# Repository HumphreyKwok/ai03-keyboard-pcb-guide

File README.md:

# A Type-C Version of ai03's Keyboard PCB Guide

Based on ai03's keyboard PCB guide and other few open sourced keyboard pcbs. </br>
I made an upgrade version with a usb type-c connector.

### Directory Lists
* ai03-pad-original </br>
The original contents of the guide created by ai03, including the schematic symbols and footprints libraries.

* ai03-pad-duplicate </br>
Simply a duplicated version of the oringinal PCB, I tried to recreate it step by step.

* ai03-pad-type-c </br>
The upgraded (?) version of the pad, with type-c connector.

### Useful Resources

* ai03's original guide: </br>
https://wiki.ai03.me/books/pcb-design/chapter/pcb-designer-guide

* KiCAD guide provided by Digi-Key: </br>
https://youtu.be/vaCVh2SAZY4

### Type-C QMK Keyboards I Used for References
* Plain60-c: </br>
https://github.com/Maartenwut/plain60-c

* Mullet: </br>
https://github.com/coseyfannitutti/mullet

* Remeo: </br>
https://github.com/coseyfannitutti/romeo

* CO60: </br>
https://github.com/jmdaly/CO60

This is where all my journeys starts, thanks to the community. </br>
Good luck :)

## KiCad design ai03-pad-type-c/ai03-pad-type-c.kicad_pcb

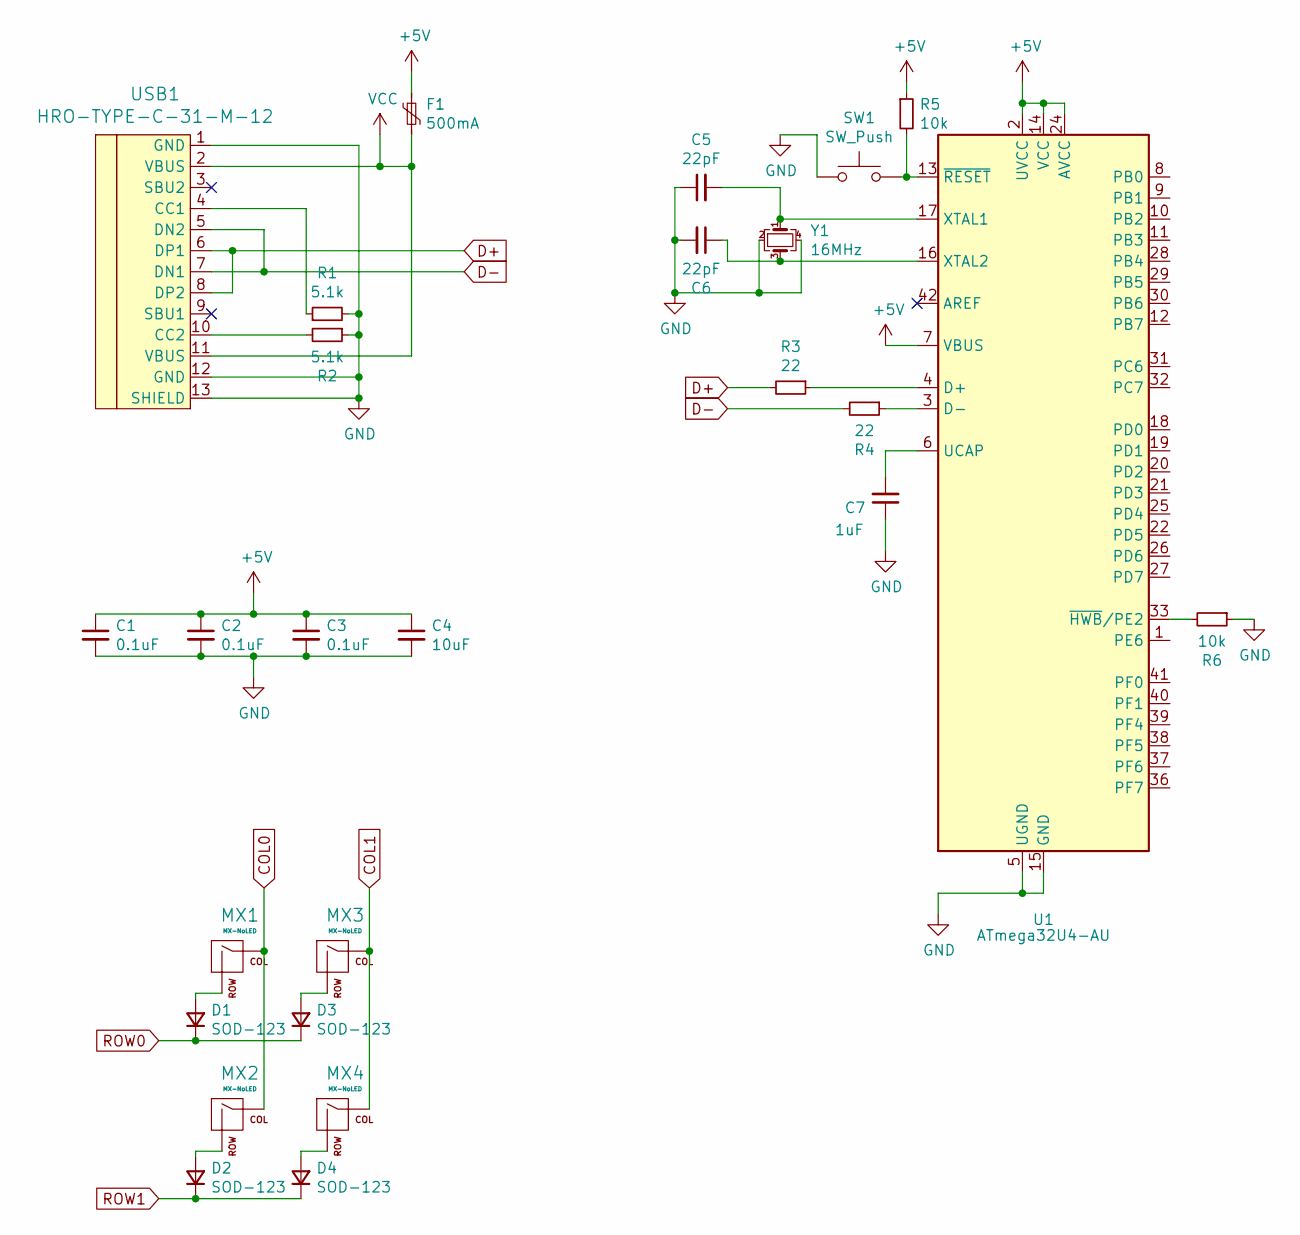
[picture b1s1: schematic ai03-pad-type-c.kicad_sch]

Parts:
C1, C2, C3: 0.1uF; C_0805_2012Metric
C4: 10uF; C_0805_2012Metric
C5, C6: 22pF; C_0805_2012Metric
C7: 1uF; C_0805_2012Metric
D1, D2, D3, D4: SOD-123; D_SOD-123
F1: 500mA; Fuse_1206_3216Metric
MX1, MX2, MX3, MX4: MX-NoLED; MXOnly-1U-NoLED
R1, R2: 5.1k; R_0805_2012Metric
R3, R4: 22; R_0805_2012Metric
R5, R6: 10k; R_0805_2012Metric
SW1: SW_Push; SKQG-1155865
U1: ATmega32U4-AU; TQFP-44_10x10mm_P0.8mm
USB1: HRO-TYPE-C-31-M-12
Y1: 16MHz; Crystal_SMD_3225-4Pin_3.2x2.5mm

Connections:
+5V: C1.1, C2.1, C3.1, C4.1, F1.1, R5.1, U1.2 (UVCC), U1.7 (VBUS), U1.14 (VCC), U1.24 (AVCC), U1.34 (VCC), U1.44 (AVCC)
COL0: MX1.1 (COL), MX2.1 (COL), U1.10 (PB2)
COL1: MX3.1 (COL), MX4.1 (COL), U1.8 (PB0)
D+: R3.2, USB1.6 (DP1), USB1.8 (DP2)
D-: R4.2, USB1.5 (DN2), USB1.7 (DN1)
GND: C1.2, C2.2, C3.2, C4.2, C5.1, C6.2, C7.1, R1.2, R2.1, R6.1, SW1.1, U1.5 (UGND), U1.15 (GND), U1.23 (GND), U1.35 (GND), U1.43 (GND), USB1.1 (GND), USB1.12 (GND), USB1.13 (SHIELD), Y1.2, Y1.4
unnamed: C5.2, U1.17 (XTAL1), Y1.1
unnamed: C6.1, U1.16 (XTAL2), Y1.3
unnamed: C7.2, U1.6 (UCAP)
unnamed: D1.2 (A), MX1.2 (ROW)
unnamed: D2.2 (A), MX2.2 (ROW)
unnamed: D3.2 (A), MX3.2 (ROW)
unnamed: D4.2 (A), MX4.2 (ROW)
unnamed: R1.1, USB1.4 (CC1)
unnamed: R2.2, USB1.10 (CC2)
unnamed: R3.1, U1.4 (D+)
unnamed: R4.1, U1.3 (D-)
unnamed: R5.2, SW1.2, U1.13 (~RESET)
unnamed: R6.2, U1.33 (~HWB~/PE2)
ROW0: D1.1 (K), D3.1 (K), U1.9 (PB1)
ROW1: D2.1 (K), D4.1 (K), U1.11 (PB3)
VCC: F1.2, USB1.2 (VBUS), USB1.11 (VBUS)

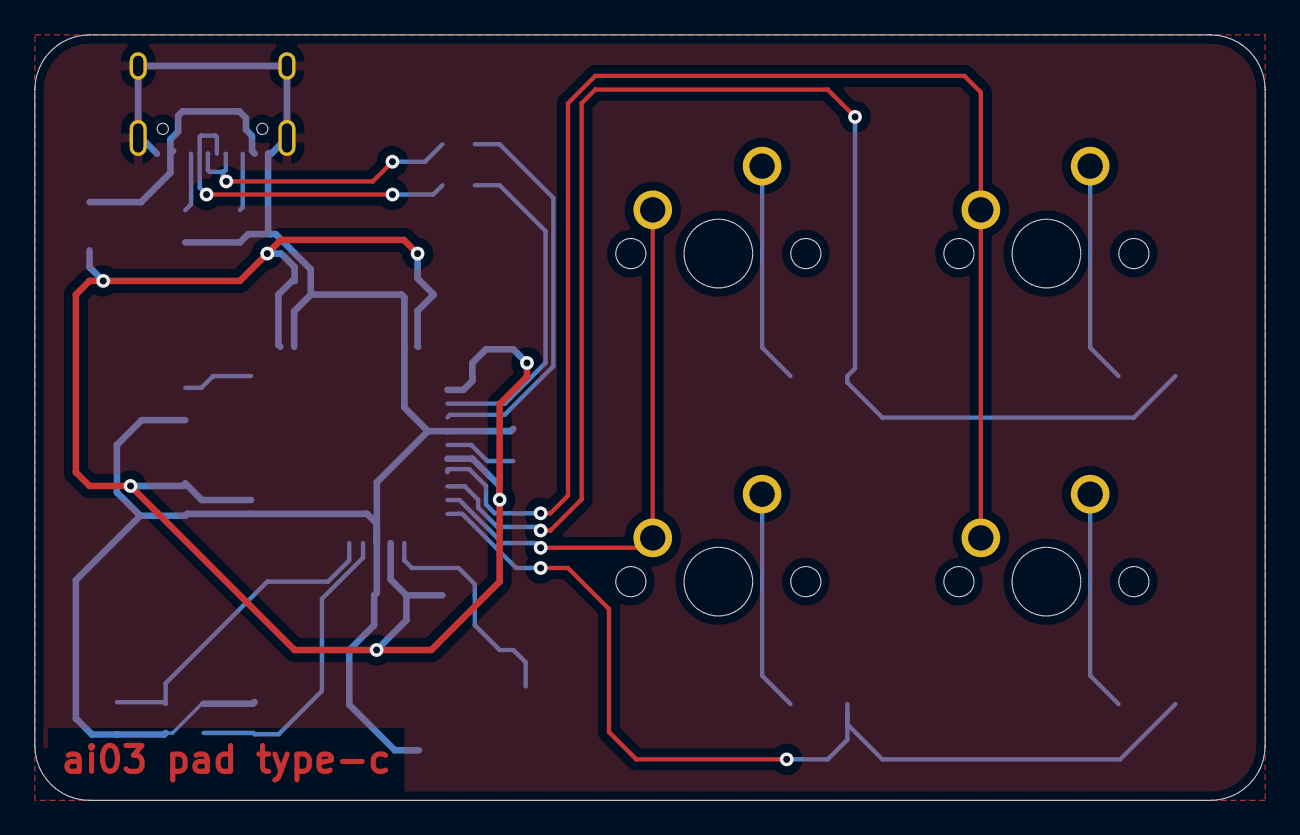
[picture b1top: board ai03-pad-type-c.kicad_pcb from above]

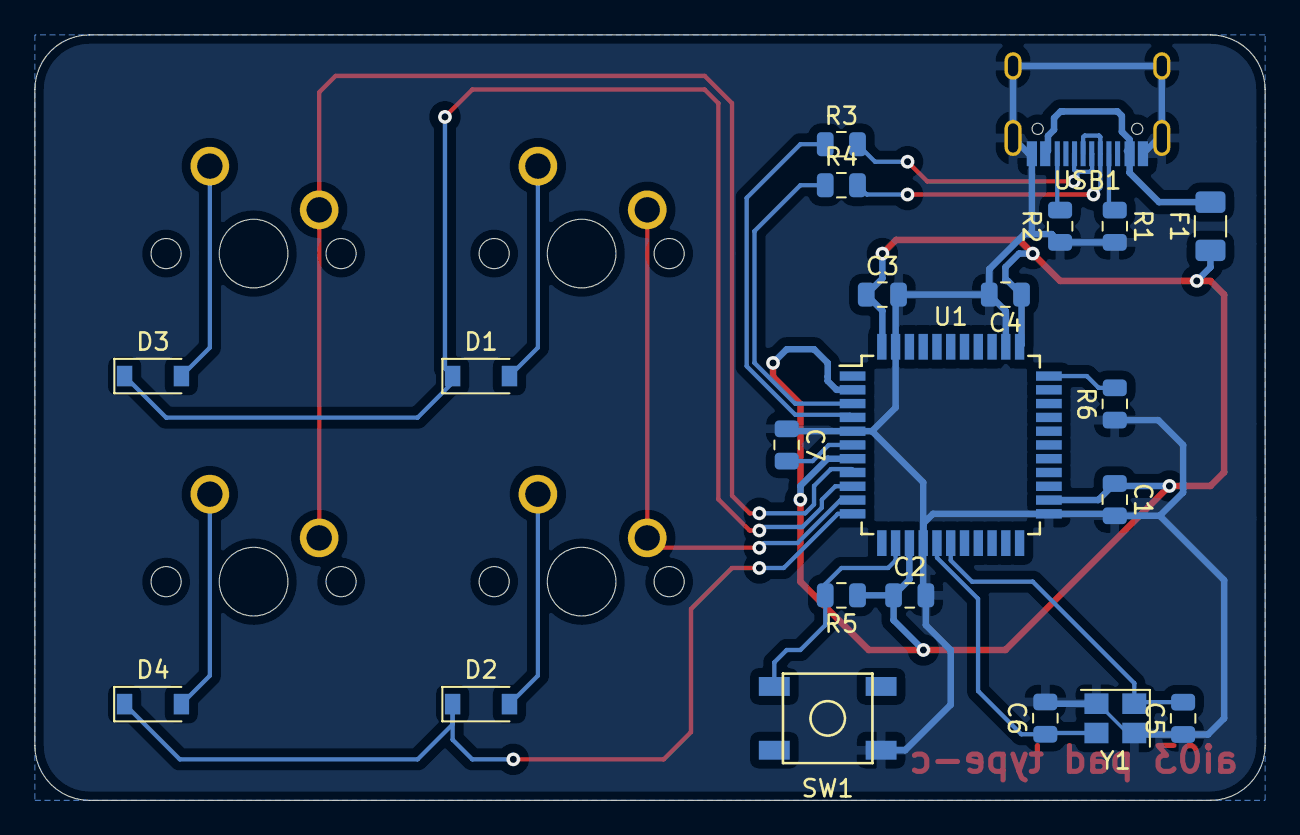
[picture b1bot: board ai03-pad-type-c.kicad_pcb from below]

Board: 2 copper layers, 71.4 x 44.5 mm, 26 parts (22 on the bottom side), 22 nets.

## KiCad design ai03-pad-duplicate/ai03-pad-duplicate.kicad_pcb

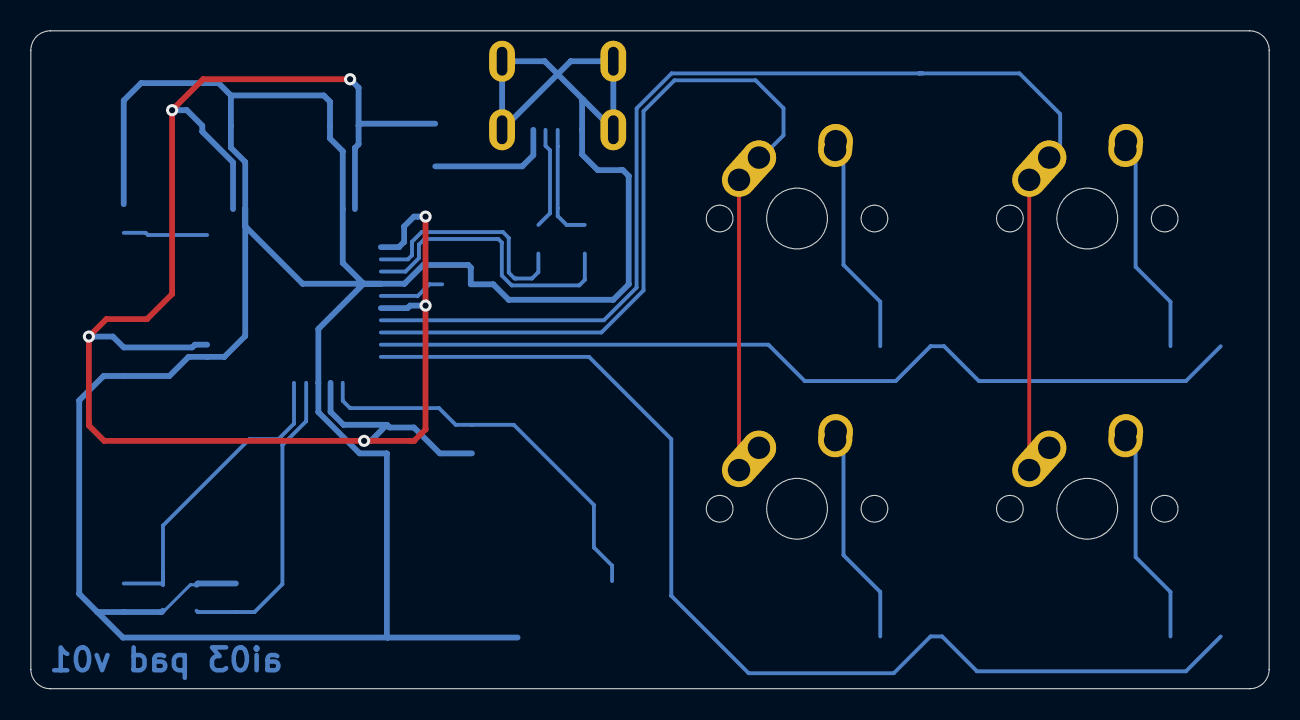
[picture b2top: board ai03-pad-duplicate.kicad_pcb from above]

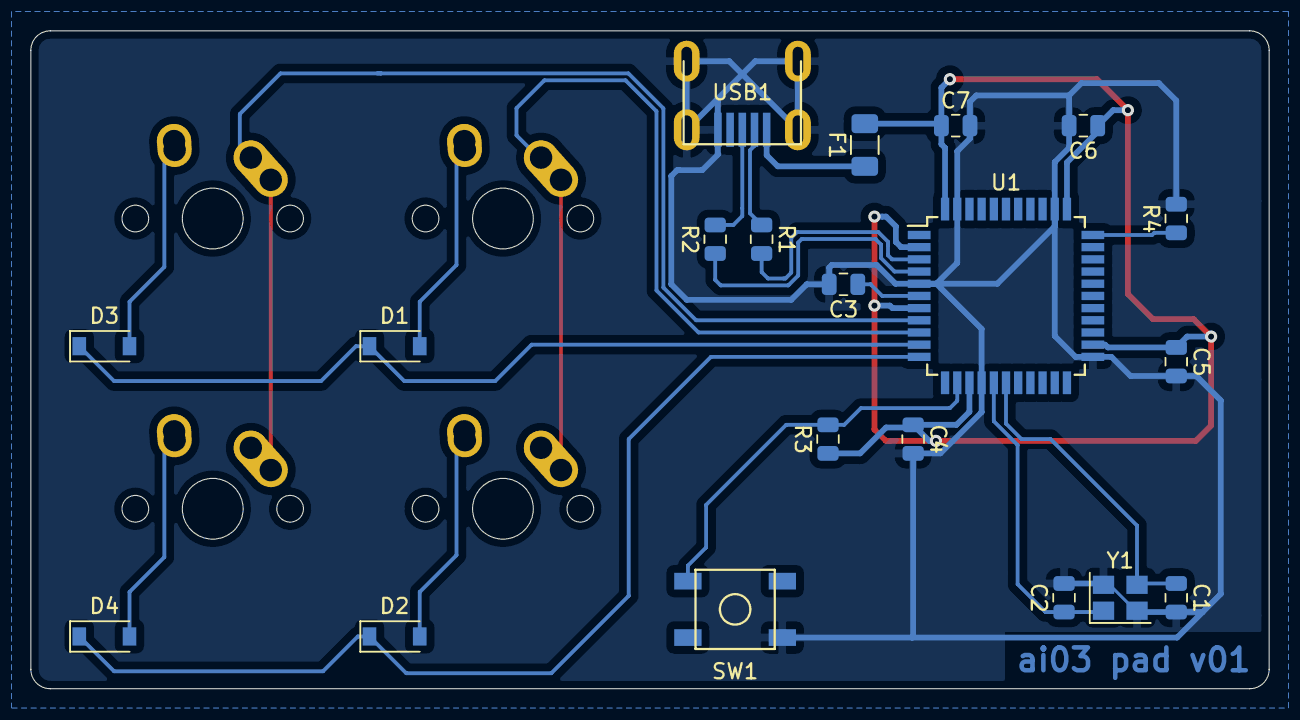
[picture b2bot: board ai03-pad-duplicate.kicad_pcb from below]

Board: 2 copper layers, 81.3 x 43.2 mm, 24 parts (20 on the bottom side), 20 nets.

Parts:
C1, C2: 22pF; C_0805_2012Metric
C3: 1uF; C_0805_2012Metric
C4, C5, C6: 0.1uF; C_0805_2012Metric
C7: 10uf; C_0805_2012Metric
D1, D2, D3, D4: D_Small; D_SOD-123
F1: 500mA; Fuse_1206_3216Metric
MX1, MX2, MX3, MX4: MX-NoLED; MX-1U-NoLED
R1, R2: 22; R_0805_2012Metric
R3, R4: 10k; R_0805_2012Metric
SW1: SW_Push; SKQG-1155865
U1: ATmega32U4-AU; TQFP-44_10x10mm_P0.8mm
USB1: Molex-0548190589
Y1: 16MHz; Crystal_SMD_3225-4Pin_3.2x2.5mm

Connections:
+5V: C4.1, C5.1, C6.1, C7.1, F1.2, R3.1, U1.2 (UVCC), U1.7 (VBUS), U1.14 (VCC), U1.24 (AVCC), U1.34 (VCC), U1.44 (AVCC)
COL0: MX1.1 (COL), MX2.1 (COL), U1.9 (PB1)
COL1: MX3.1 (COL), MX4.1 (COL), U1.8 (PB0)
D+: R2.2, USB1.3 (D+)
D-: R1.1, USB1.4 (D-)
GND: C1.2, C2.2, C3.2, C4.2, C5.2, C6.2, C7.2, R4.2, SW1.1, U1.5 (UGND), U1.15 (GND), U1.23 (GND), U1.35 (GND), U1.43 (GND), USB1.1 (GND), USB1.6 (SHIELD), Y1.2, Y1.4
unnamed: C1.1, U1.17 (XTAL1), Y1.3
unnamed: C2.1, U1.16 (XTAL2), Y1.1
unnamed: C3.1, U1.6 (UCAP)
unnamed: D1.2 (A), MX1.2 (ROW)
unnamed: D2.2 (A), MX2.2 (ROW)
unnamed: D3.2 (A), MX3.2 (ROW)
unnamed: D4.2 (A), MX4.2 (ROW)
unnamed: R1.2, U1.3 (D-)
unnamed: R2.1, U1.4 (D+)
unnamed: R3.2, SW1.2, U1.13 (~RESET)
unnamed: R4.1, U1.33 (~HWB~/PE2)
ROW0: D1.1 (K), D3.1 (K), U1.10 (PB2)
ROW1: D2.1 (K), D4.1 (K), U1.11 (PB3)
VCC: F1.1, USB1.5 (VBUS)

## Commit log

2020-06-12 Updated the readme file
2020-06-12 imported the schematic symbols nd footprints libraries
2020-06-12 Finish the MCU schematic
2020-06-13 Complete the schematic
2020-06-15 Complete the PCB
2020-06-17 Compete the type-c PCB
